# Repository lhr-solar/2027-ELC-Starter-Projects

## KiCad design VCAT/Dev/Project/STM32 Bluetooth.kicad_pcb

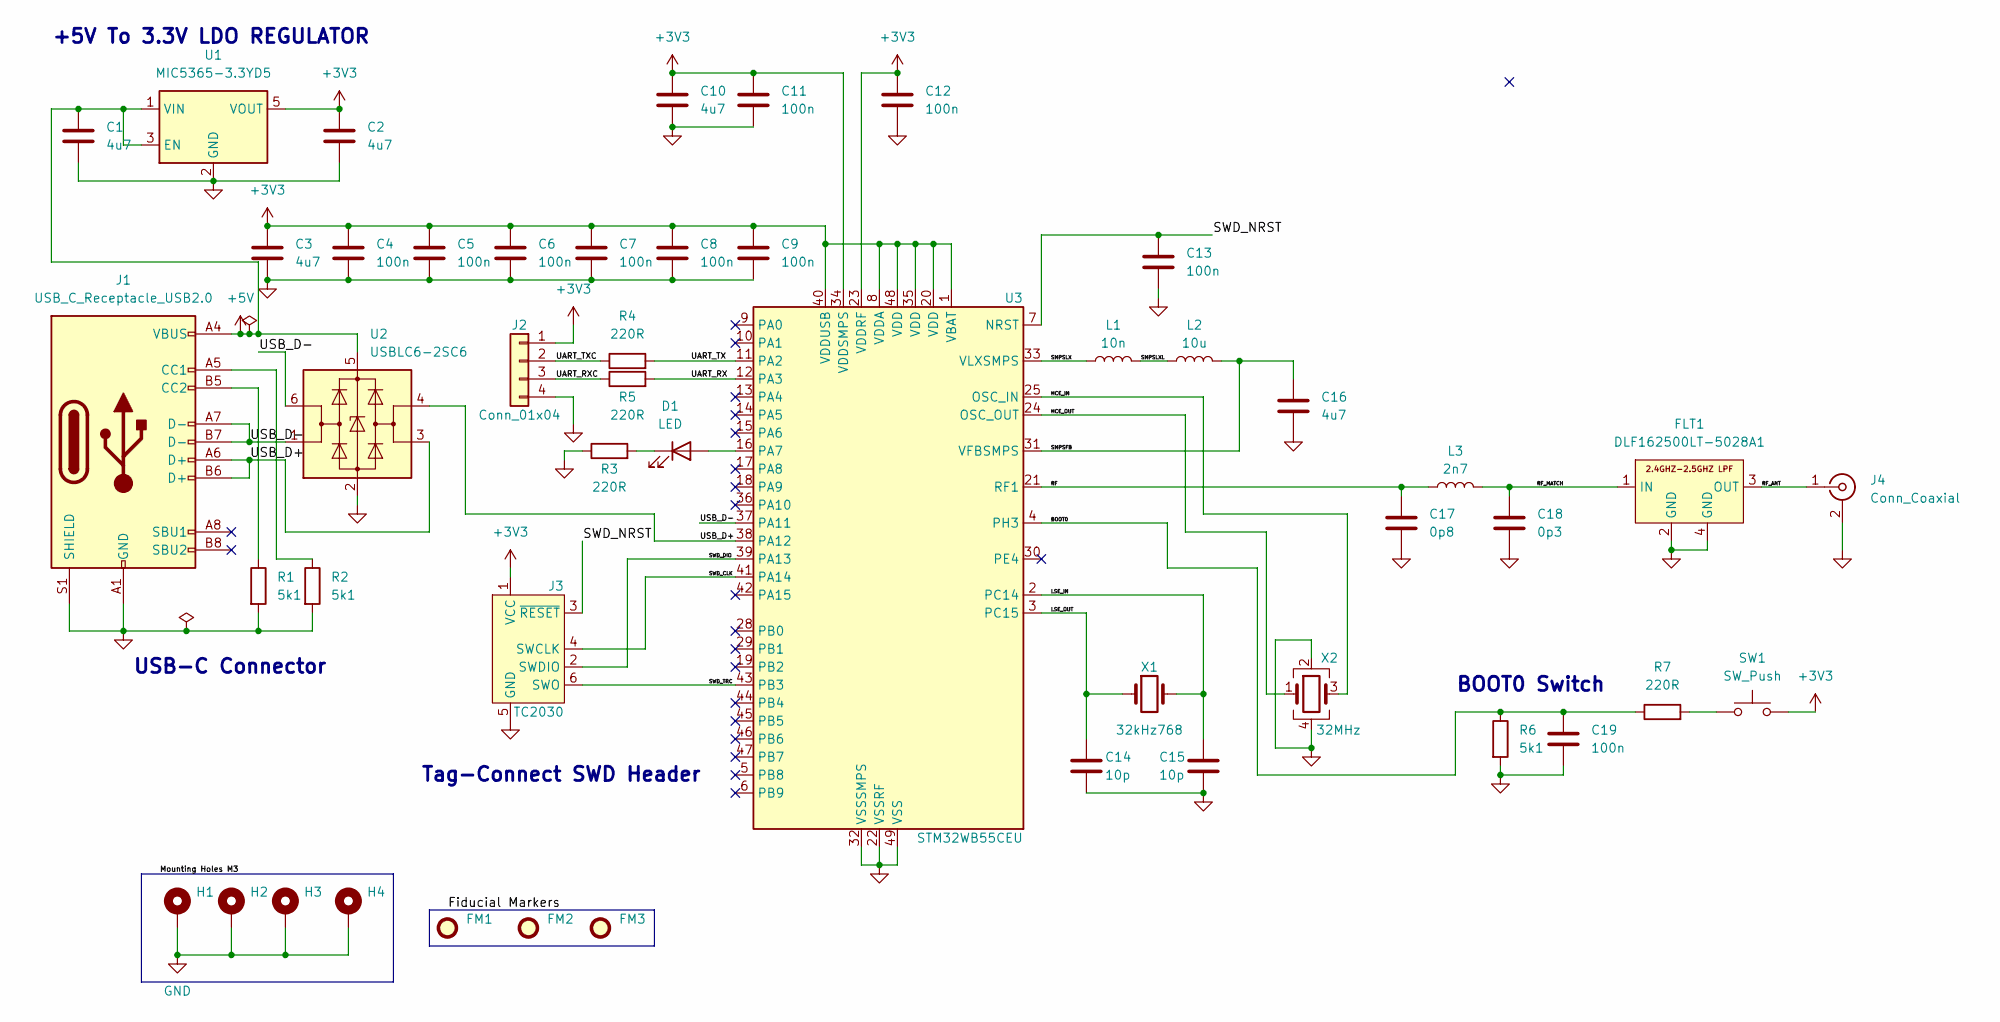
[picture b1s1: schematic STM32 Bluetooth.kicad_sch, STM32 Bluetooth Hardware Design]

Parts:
C1, C2, C3, C10, C16: 4u7; C_0603_1608Metric
C4, C5, C6, C7, C8, C9, C11, C12, C13, C19: 100n; C_0402_1005Metric
C14, C15: 10p; C_0402_1005Metric
C17: 0p8; C_0402_1005Metric
C18: 0p3; C_0402_1005Metric
D1: LED; LED_0402_1005Metric
FLT1: DLF162500LT-5028A1
FM1, FM2, FM3: Fiducial; Fiducial_1mm_Mask2mm
H1, H2, H3, H4: MountingHole_Pad; MountingHole_2.2mm_M2_Pad
J1: USB_C_Receptacle_USB2.0; USB_C_Receptacle_GCT_USB4105-xx-A_16P_TopMnt_Horizontal
J2: Conn_01x04; Molex_PicoBlade_53048-0410_1x04_P1.25mm_Horizontal
J3: TC2030; Tag-Connect_TC2030-IDC-FP_2x03_P1.27mm_Vertical
J4: Conn_Coaxial; U.FL_Hirose_U.FL-R-SMT-1_Vertical
L1: 10n; L_0402_1005Metric
L2: 10u; L_0805_2012Metric
L3: 2n7; L_0402_1005Metric
R1, R2, R6: 5k1; R_0402_1005Metric
R3, R4, R5, R7: 220R; R_0402_1005Metric
SW1: SW_Push; SW_SPST_CK_RS282G05A3
U1: MIC5365-3.3YD5; SOT-23-5
U2: USBLC6-2SC6; SOT-23-6
U3: STM32WB55CEU; QFN-48-1EP_7x7mm_P0.5mm_EP5.6x5.6mm
X1: 32kHz768; Crystal_SMD_2012-2Pin_2.0x1.2mm
X2: 32MHz; Crystal_SMD_2016-4Pin_2.0x1.6mm

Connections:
+3V3: C2.1, C3.1, C4.1, C5.1, C6.1, C7.1, C8.1, C9.1, C10.1, C11.1, C12.1, J2.1, J3.1 (VCC), SW1.2, U1.5 (VOUT), U3.1 (VBAT), U3.8 (VDDA), U3.20 (VDD), U3.23 (VDDRF), U3.34 (VDDSMPS), U3.35 (VDD), U3.40 (VDDUSB), U3.48 (VDD)
+5V: C1.1, J1.A4 (VBUS), J1.A9 (VBUS), J1.B4 (VBUS), J1.B9 (VBUS), U1.1 (VIN), U1.3 (EN), U2.5 (VBUS)
/BOOT0: C19.1, R6.1, R7.1, U3.4 (PH3)
/HCE_IN: U3.25 (OSC_IN), X2.3
/HCE_OUT: U3.24 (OSC_OUT), X2.1
/LSE_IN: C15.1, U3.2 (PC14), X1.2
/LSE_OUT: C14.1, U3.3 (PC15), X1.1
/RF: C17.1, L3.1, U3.21 (RF1)
/RF_ANT: FLT1.3 (OUT), J4.1 (In)
/RF_MATCH: C18.1, FLT1.1 (IN), L3.2
/SMPSFB: C16.1, L2.2, U3.31 (VFBSMPS)
/SMPSLX: L1.1, U3.33 (VLXSMPS)
/SMPSLXL: L1.2, L2.1
/SWD_CLK: J3.4 (SWCLK), U3.41 (PA14)
/SWD_DIO: J3.2 (SWDIO), U3.39 (PA13)
/SWD_NRST: C13.1, J3.3 (~RESET), U3.7 (NRST)
/SWD_TRC: J3.6 (SWO), U3.43 (PB3)
/UART_RX: R5.2, U3.12 (PA3)
/UART_RXC: J2.3, R5.1
/UART_TX: R4.2, U3.11 (PA2)
/UART_TXC: J2.2, R4.1
/USB_D+: J1.A6 (D+), J1.B6 (D+), U2.3 (I/O2), U2.4 (I/O2), U3.38 (PA12)
/USB_D-: J1.A7 (D-), J1.B7 (D-), U2.1 (I/O1), U2.6 (I/O1), U3.37 (PA11)
GND: C1.2, C2.2, C3.2, C4.2, C5.2, C6.2, C7.2, C8.2, C9.2, C10.2, C11.2, C12.2, C13.2, C14.2, C15.2, C16.2, C17.2, C18.2, C19.2, FLT1.2 (GND), FLT1.4 (GND), H1.1 (1_1), H2.1 (1_1), H3.1 (1_1), H4.1 (1_1), J1.A1 (GND), J1.A12 (GND), J1.B1 (GND), J1.B12 (GND), J1.S1 (SHIELD), J2.4, J3.5 (GND), J4.2 (Ext), R1.2, R2.2, R3.1, R6.2, U1.2 (GND), U2.2 (GND), U3.22 (VSSRF), U3.32 (VSSSMPS), U3.49 (VSS), X2.2, X2.4
unnamed: D1.2 (A), U3.16 (PA7)
unnamed: D1.1 (K), R3.2
unnamed: J1.A5 (CC1), R2.1
unnamed: J1.B5 (CC2), R1.1
unnamed: R7.2, SW1.1

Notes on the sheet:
Tag-Connect SWD Header
BOOT0 Switch
+5V To 3.3V LDO REGULATOR
USB-C Connector

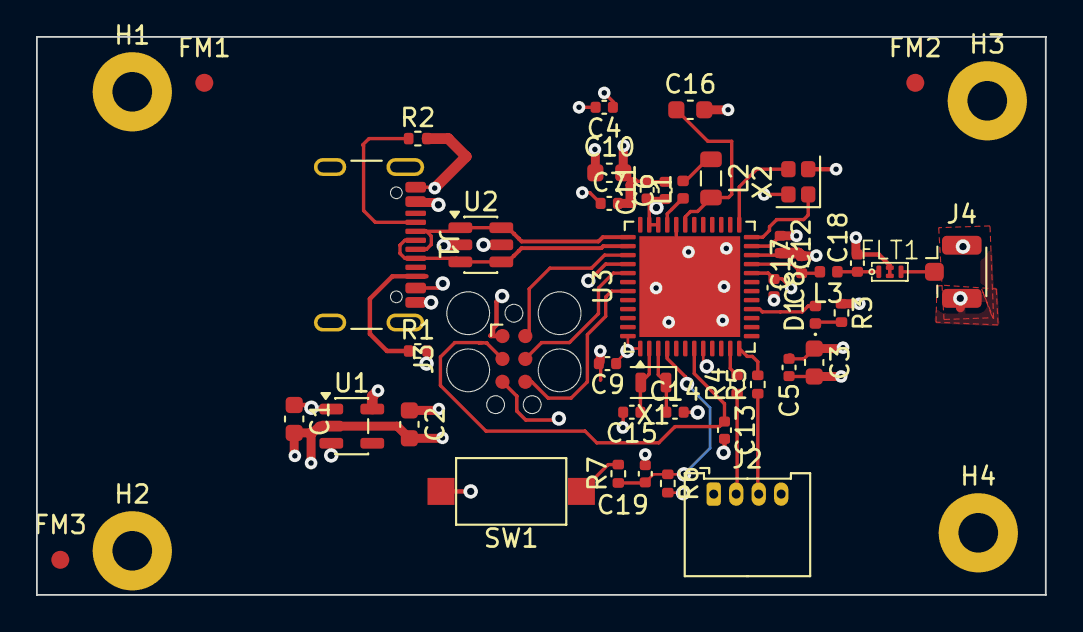
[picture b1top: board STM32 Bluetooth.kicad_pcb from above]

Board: 4 copper layers, 56.1 x 31.0 mm, 48 parts (0 on the bottom side), 29 nets.

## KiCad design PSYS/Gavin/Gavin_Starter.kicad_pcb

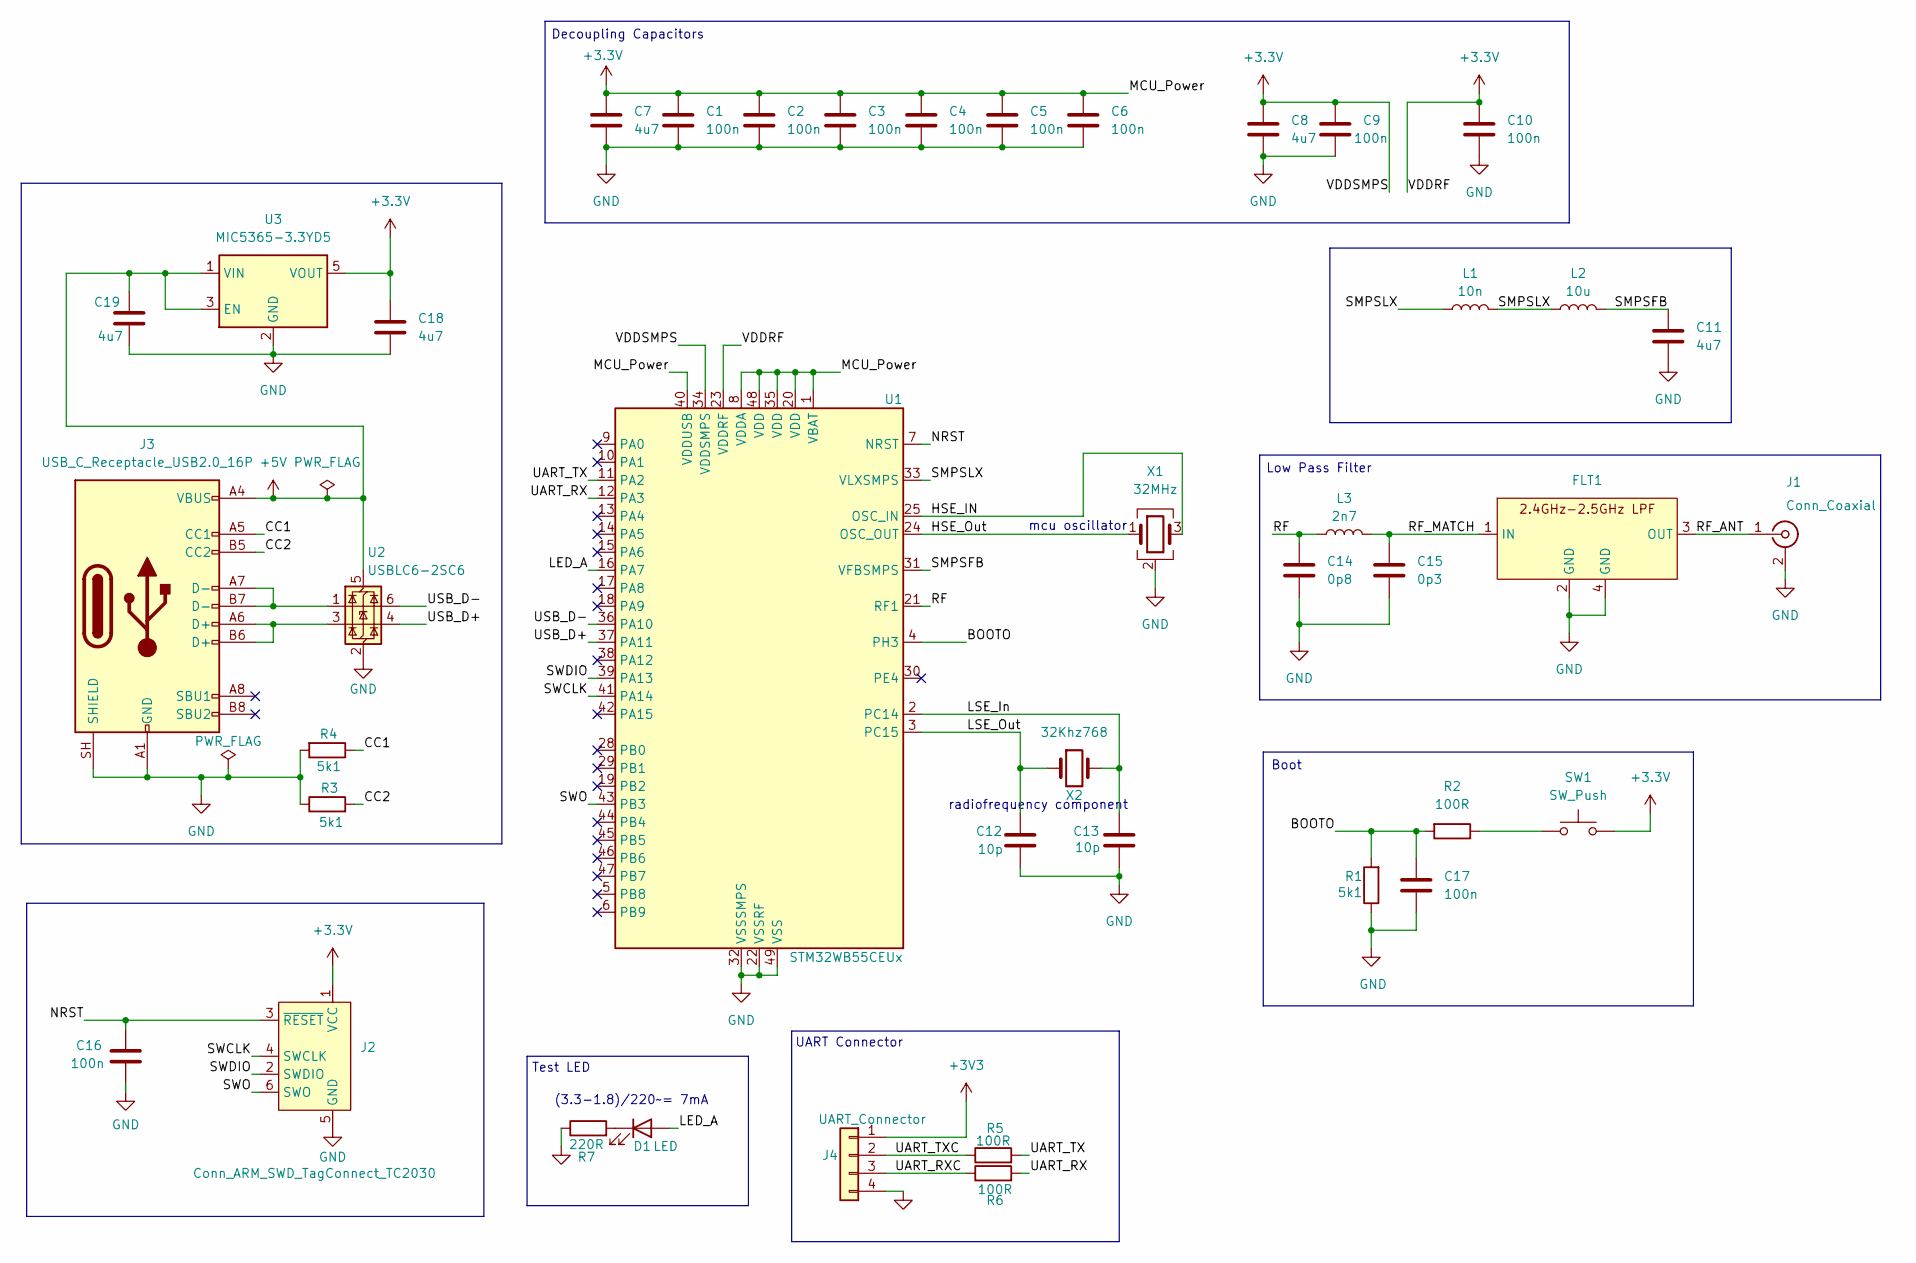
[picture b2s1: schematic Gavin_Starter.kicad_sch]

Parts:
C1, C2, C3, C4, C5, C6, C9, C10, C16, C17: 100n; C_0402_1005Metric
C7, C8, C11, C18, C19: 4u7; C_0603_1608Metric
C12, C13: 10p; C_0402_1005Metric
C14: 0p8; C_0402_1005Metric
C15: 0p3; C_0402_1005Metric
D1: LED; LED_0402_1005Metric
FLT1: DLF162500LT-5028A1
J1: Conn_Coaxial; U.FL_Hirose_U.FL-R-SMT-1_Vertical
J2: Conn_ARM_SWD_TagConnect_TC2030; Tag-Connect_TC2030-IDC-FP_2x03_P1.27mm_Vertical
J3: USB_C_Receptacle_USB2.0_16P; USB_C_Receptacle_GCT_USB4105-xx-A_16P_TopMnt_Horizontal
J4: UART_Connector; Molex_PicoBlade_53048-0410_1x04_P1.25mm_Horizontal
L1: 10n; L_0402_1005Metric
L2: 10u; L_0805_2012Metric
L3: 2n7; L_0402_1005Metric
R1, R3, R4: 5k1; R_0402_1005Metric
R2, R5, R6: 100R; R_0402_1005Metric
R7: 220R; R_0402_1005Metric
SW1: SW_Push; SW_Push_1P1T_NO_CK_KMR2
U1: STM32WB55CEUx; QFN-48-1EP_7x7mm_P0.5mm_EP5.6x5.6mm
U2: USBLC6-2SC6; SOT-23-6
U3: MIC5365-3.3YD5; TSOT-23-5
X1: 32MHz; Crystal_SMD_2016-4Pin_2.0x1.6mm
X2: 32Khz768; Crystal_SMD_2012-2Pin_2.0x1.2mm

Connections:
+3.3V: C1.1, C2.1, C3.1, C4.1, C5.1, C6.1, C7.1, C8.1, C9.1, C10.1, C18.1, J2.1 (VCC), SW1.2, U1.1 (VBAT), U1.8 (VDDA), U1.20 (VDD), U1.23 (VDDRF), U1.34 (VDDSMPS), U1.35 (VDD), U1.40 (VDDUSB), U1.48 (VDD), U3.5 (VOUT)
+3V3: J4.1
+5V: C19.1, J3.A4 (VBUS), J3.A9 (VBUS), J3.B4 (VBUS), J3.B9 (VBUS), U2.5 (VBUS), U3.1 (VIN), U3.3 (EN)
/BOOTO: C17.1, R1.2, R2.2, U1.4 (PH3)
/CC1: J3.A5 (CC1), R4.1
/CC2: J3.B5 (CC2), R3.2
/HSE_IN: U1.25 (OSC_IN), X1.3
/HSE_Out: U1.24 (OSC_OUT), X1.1
/LED_A: D1.2 (A), U1.16 (PA7)
/LSE_In: C13.1, U1.2 (PC14), X2.2
/LSE_Out: C12.1, U1.3 (PC15), X2.1
/NRST: C16.1, J2.3 (~RESET), U1.7 (NRST)
/RF: C14.1, L3.1, U1.21 (RF1)
/RF_ANT: FLT1.3 (OUT), J1.1 (In)
/RF_MATCH: C15.1, FLT1.1 (IN), L3.2
/SMPSFB: C11.1, L2.2, U1.31 (VFBSMPS)
/SMPSLX: L1.1, L1.2, L2.1, U1.33 (VLXSMPS)
/SWCLK: J2.4 (SWCLK), U1.41 (PA14)
/SWDIO: J2.2 (SWDIO), U1.39 (PA13)
/SWO: J2.6 (SWO), U1.43 (PB3)
/UART_RX: R6.2, U1.12 (PA3)
/UART_RXC: J4.3, R6.1
/UART_TX: R5.2, U1.11 (PA2)
/UART_TXC: J4.2, R5.1
/USB_D+: U1.37 (PA11), U2.4 (I/O2)
/USB_D-: U1.36 (PA10), U2.6 (I/O1)
GND: C1.2, C2.2, C3.2, C4.2, C5.2, C6.2, C7.2, C8.2, C9.2, C10.2, C11.2, C12.2, C13.2, C14.2, C15.2, C16.2, C17.2, C18.2, C19.2, FLT1.2 (GND), FLT1.4 (GND), J1.2 (Ext), J2.5 (GND), J3.A1 (GND), J3.A12 (GND), J3.B1 (GND), J3.B12 (GND), J3.SH (SHIELD), J4.4, R1.1, R3.1, R4.2, R7.1, U1.22 (VSSRF), U1.32 (VSSSMPS), U1.49 (VSS), U2.2 (GND), U3.2 (GND), X1.2 (G), X1.4 (G)
unnamed: D1.1 (K), R7.2
unnamed: J3.A6 (D+), J3.B6 (D+), U2.3 (I/O2)
unnamed: J3.A7 (D-), J3.B7 (D-), U2.1 (I/O1)
unnamed: R2.1, SW1.1

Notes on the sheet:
(3.3-1.8)/220~= 7mA
mcu oscillator
Decoupling Capacitors
Test LED
Low Pass Filter
UART Connector
radiofrequency component
Boot

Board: 4 copper layers, 41 parts (0 on the bottom side), 30 nets, no tracks yet.

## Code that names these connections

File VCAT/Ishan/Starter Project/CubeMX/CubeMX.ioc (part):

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Mcu.Name=STM32WB55CEUx
Mcu.Package=UFQFPN48
Mcu.UserName=STM32WB55CEUx
PA11.Mode=Device
PA11.Signal=USB_DM
PA12.Mode=Device
PA12.Signal=USB_DP
PA13.Mode=Trace_Asynchronous_SW
PA13.Signal=SYS_JTMS-SWDIO
PA14.Mode=Trace_Asynchronous_SW
PA14.Signal=SYS_JTCK-SWCLK
PA2.Mode=Asynchronous
PA2.Signal=LPUART1_TX
PA3.Mode=Asynchronous
PA3.Signal=LPUART1_RX
PA7.Signal=S_TIM17_CH1
PB3.Mode=Trace_Asynchronous_SW
PB3.Signal=SYS_JTDO-SWO
PC14-OSC32_IN.Mode=LSE-External-Oscillator
PC14-OSC32_IN.Signal=RCC_OSC32_IN
PC15-OSC32_OUT.Mode=LSE-External-Oscillator
PC15-OSC32_OUT.Signal=RCC_OSC32_OUT
RCC.HSE_VALUE=8000000
RCC.SYSCLKFreq_VALUE=64000000
RCC.SYSCLKSource=RCC_SYSCLKSOURCE_PLLCLK
board=custom
